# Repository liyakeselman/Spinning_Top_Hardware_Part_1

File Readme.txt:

Directories:
WEB
Sch
Program
ProductionFiles
Pres
KiCad
ErrorSheet
DOC
Data_sh
ComponentsList
BOM
3D_PrintFiles
3D_Fusion360Files
LICENSE.txt

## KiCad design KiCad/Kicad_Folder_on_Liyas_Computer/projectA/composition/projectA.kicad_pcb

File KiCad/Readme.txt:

content:
geometry.dxf
KiCad_Settings_Configuration.pdf
projectA.kicad_pcb
projectA.kicad_pro
projectA.kicad_sch
Directory:
Kicad_Folder_on_Liyas_Computer

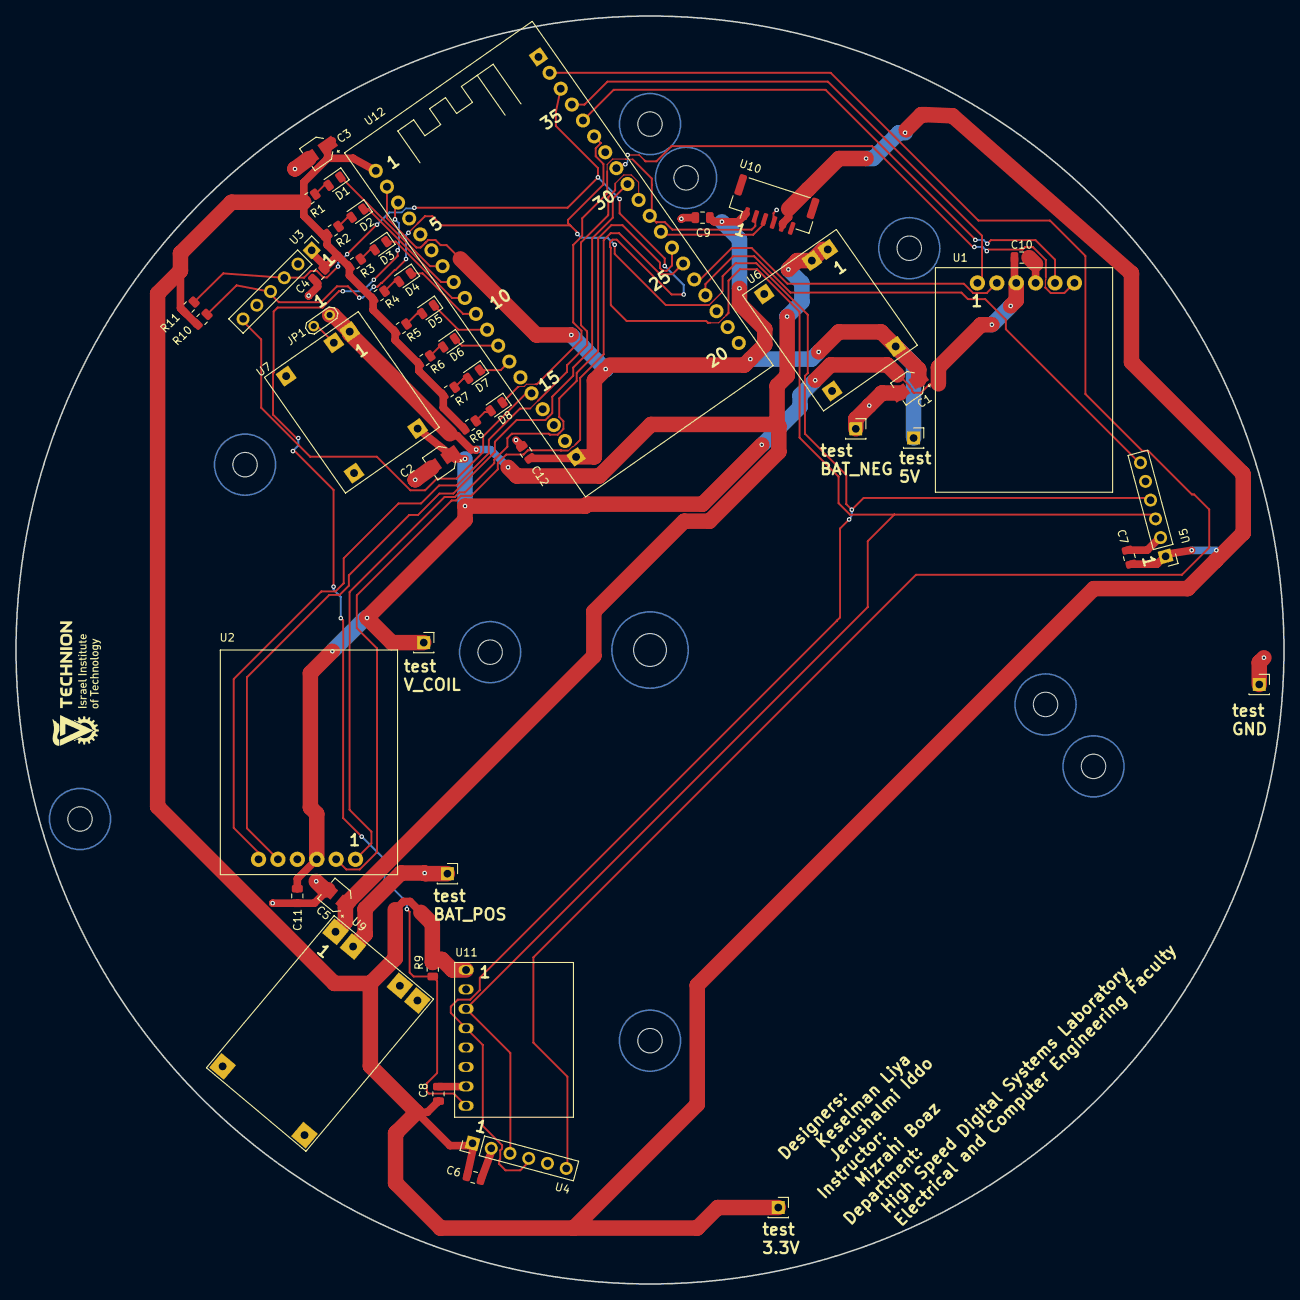
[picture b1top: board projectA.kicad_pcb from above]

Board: 2 copper layers, 166.0 x 166.0 mm, 50 parts (1 on the bottom side), 38 nets.

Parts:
8U: BATTERY_HOLDER
C1, C2, C3, C5: 47uF; CP_Elec_3x5.3
C4, C6, C7, C8, C9, C10, C11, C12: 10uF; C_0805_2012Metric
D1, D2, D3, D4, D5, D6, D7, D8: CD4148W; D_0805_2012Metric
JP1: Jumper_2_Bridged; TestPoint_2Pads_Pitch2.54mm_Drill0.8mm
R1, R2, R3, R4, R5, R6, R7, R8: 330; R_0805_2012Metric
R9, R10, R11: 3.3K; R_0805_2012Metric
TP1: TestPoint_3.3V; PinSocket_1x01_P2.54mm_Vertical
TP2: TestPoint_5V; PinSocket_1x01_P2.54mm_Vertical
TP3: TestPoint_VCoil; PinSocket_1x01_P2.54mm_Vertical
TP4: TestPoint_GND; PinSocket_1x01_P2.54mm_Vertical
TP5: TestPoint_Battery_POS; PinSocket_1x01_P2.54mm_Vertical
TP6: TestPoint_Battery_NEG; PinSocket_1x01_P2.54mm_Vertical
U1, U2: MOTOR_DRIVER
U3, U4, U5: VL53L0XV2
U6, U7: BUCK_BOOST
U9: CHARGE_CONTROLLER
U10: TF_LUNA
U11: MPU6050
U12: ESP32

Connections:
+3.3V: C3.1, C4.2, C6.2, C7.2, C8.2, R1.2, R2.2, R3.2, R4.2, R5.2, R6.2, R7.2, R8.2, R9.1, R10.1, R11.1, TP1.1, U3.1 (VIN), U4.1 (VIN), U5.1 (VIN), U10.5 (CONFIGURATION_INPUT), U11.1 (VCC), U12.1 (3V3)
+5V: C1.1, C9.2, C12.2, TP2.1, U6.4 (OUT_P), U10.1 (5V), U12.2 (RESTART__EN), U12.19 (5V)
+9V: C2.1, C10.1, C11.1, TP3.1, U1.3 (VCC), U2.3 (VCC), U7.4 (OUT_P)
/BB_EN: JP1.2 (B), U7.2 (EN)
/CHRG_BAT_POS: 8U.P (POS), TP5.1, U9.2 (B_P)
/CHRG_BB_IN_P: C5.1, JP1.1 (A), U6.1 (IN_P), U6.2 (EN), U7.1 (IN_P), U9.1 (OUT_P)
/ESP_LED1: D1.1 (K), U12.7 (TOUCH_9__ADC1_4__RTC_GPIO9_GPIO32)
/ESP_LED2: D2.1 (K), U12.8 (TOUCH_8__ADC1_5__RTC_GPIO8_GPIO33)
/ESP_LED3: D3.1 (K), U12.9 (DAC_1__ADC2_8__RTC_GPIO6__GPIO25)
/ESP_LED4: D4.1 (K), U12.10 (DAC_2__ADC2_9__RTC_GPIO7__GPIO26)
/ESP_LED5: D5.1 (K), U12.11 (TOUCH_7__ADC2_7__RTC_GPIO17__GPIO27)
/ESP_LED6: D6.1 (K), U12.12 (SC_CLK__HSPI_CLK__TOUCH_6__ADC2_6__RTC_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)
/ESP_LED7: D7.1 (K), U12.13 (SD_DAT2__HSPI_MISO__TOUCH_5__ADC2_5__RT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)
/ESP_LUNA_LED8_TXD: D8.1 (K), U10.2 (RXD_SDA), U12.28 (GPIO17__TX2)
/ESP_MD_A_AIA: U1.2 (A_IA), U12.24 (GPIO2__RTC_GPIO12__ADC2_2__TOUCH_2__SD_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)
/ESP_MD_A_AIB: U1.1 (A_IB), U12.35 (GPIO1__TX0)
/ESP_MD_A_BIA: U1.6 (B_IA), U12.31 (GPIO19__VSPI_MISO)
/ESP_MD_A_BIB: U1.5 (B_IB), U12.34 (GPIO3__RX0)
/ESP_MD_B_AIA: U2.2 (A_IA), U12.25 (GPIO0__RTC_GPIO11__ADC2_1__TOUCH_1)
/ESP_MD_B_AIB: U2.1 (A_IB), U12.26 (GPIO4__RTC_GPIO10__ADC2_0__TOUCH0__SD_D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)
/ESP_MD_B_BIA: U2.6 (B_IA), U12.29 (GPIO5__VSPI_CS)
/ESP_MD_B_BIB: U2.5 (B_IB), U12.30 (GPIO18__VSPI_CLK)
/ESP_MPU_VL_SCL: R11.2, U3.3 (SCL), U4.3 (SCL), U5.3 (SCL), U11.3 (SCL), U12.36 (GPIO22__I2C_SCL)
/ESP_MPU_VL_SDA: R10.2, U3.4 (SDA), U4.4 (SDA), U5.4 (SDA), U11.4 (SDA), U12.33 (GPIO21__I2C_SDA)
/ESP_VL_A_XSHUT: U3.6 (XSHUT), U12.15 (SD_DAT3__HSPI_MOSI__TOUCH_4__ADC2_4__RT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)
/ESP_VL_B_XSHUT: U4.6 (XSHUT), U12.37 (GPIO23__VSPI_MOSI)
/ESP_VL_C_XSHUT: U5.6 (XSHUT), U12.23 (GPIO15__RTC_GPIO13__ADC2_3__TOUCH3__SD_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)
/LUNA_ESP_RXD: U10.3 (TXD_SCL), U12.27 (GPIO16__RX2)
/MPU_ESP_INT: R9.2, U11.8 (INT), U12.3 (ADC1_0_RTC_GPIO0__GPIO36)
/R1_LED1: D1.2 (A), R1.1
/R2_LED2: D2.2 (A), R2.1
/R3_LED3: D3.2 (A), R3.1
/R4_LED4: D4.2 (A), R4.1
/R5_LED5: D5.2 (A), R5.1
/R6_LED6: D6.2 (A), R6.1
/R7_LED7: D7.2 (A), R7.1
/R8_LED8: D8.2 (A), R8.1
GND: 8U.N (NEG), C1.2, C2.2, C3.2, C4.1, C5.2, C6.1, C7.1, C8.1, C9.1, C10.2, C11.2, C12.1, TP4.1, TP6.1, U1.4 (GND), U2.4 (GND), U3.2 (GND), U4.2 (GND), U5.2 (GND), U6.3 (IN_N), U6.5 (OUT_N), U7.3 (IN_N), U7.5 (OUT_N), U9.3 (B_N), U9.4 (OUT_N), U9.6 (IN_N), U10.4 (GND), U11.2 (GND), U11.7 (AD0), U12.14 (GND1), U12.32 (GND2), U12.38 (GND3)

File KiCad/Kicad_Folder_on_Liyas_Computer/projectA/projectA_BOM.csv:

"Id";"Designator";"Footprint";"Quantity";"Designation";"Supplier and ref";
1;"R4,R2,R7,R5,R1,R8,R3,R6";"R_0805_2012Metric";8;"330";;;
2;"U1,U2";"MOTOR_DRIVER";2;"~";;;
3;"C3,C2,C5,C1";"CP_Elec_3x5.3";4;"47uF";;;
4;"TP5";"PinSocket_1x01_P2.54mm_Vertical";1;"TestPoint_Battery_POS";;;
5;"U3,U4,U5";"VL53L0XV2";3;"~";;;
6;"C12,C10,C7,C9,C8,C11,C6,C4";"C_0805_2012Metric";8;"10uF";;;
7;"D8,D2,D6,D1,D3,D5,D7,D4";"D_0805_2012Metric";8;"CD4148W";;;
8;"U11";"MPU6050";1;"~";;;
9;"U10";"TF_LUNA";1;"~";;;
10;"TP4";"PinSocket_1x01_P2.54mm_Vertical";1;"TestPoint_GND";;;
11;"R9,R10,R11";"R_0805_2012Metric";3;"3.3K";;;
12;"JP1";"TestPoint_2Pads_Pitch2.54mm_Drill0.8mm";1;"Jumper_2_Bridged";;;
13;"U7,U6";"BUCK_BOOST";2;"~";;;
14;"TP1";"PinSocket_1x01_P2.54mm_Vertical";1;"TestPoint_3.3V";;;
15;"TP6";"PinSocket_1x01_P2.54mm_Vertical";1;"TestPoint_Battery_NEG";;;
16;"U9";"CHARGE_CONTROLLER";1;"~";;;
17;"TP3";"PinSocket_1x01_P2.54mm_Vertical";1;"TestPoint_VCoil";;;
18;"TP2";"PinSocket_1x01_P2.54mm_Vertical";1;"TestPoint_5V";;;
19;"U12";"ESP32";1;"~";;;
20;"8U";"BATTERY_HOLDER";1;"~";;;

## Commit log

2025-04-09 Reupload: replace all content with clean version
